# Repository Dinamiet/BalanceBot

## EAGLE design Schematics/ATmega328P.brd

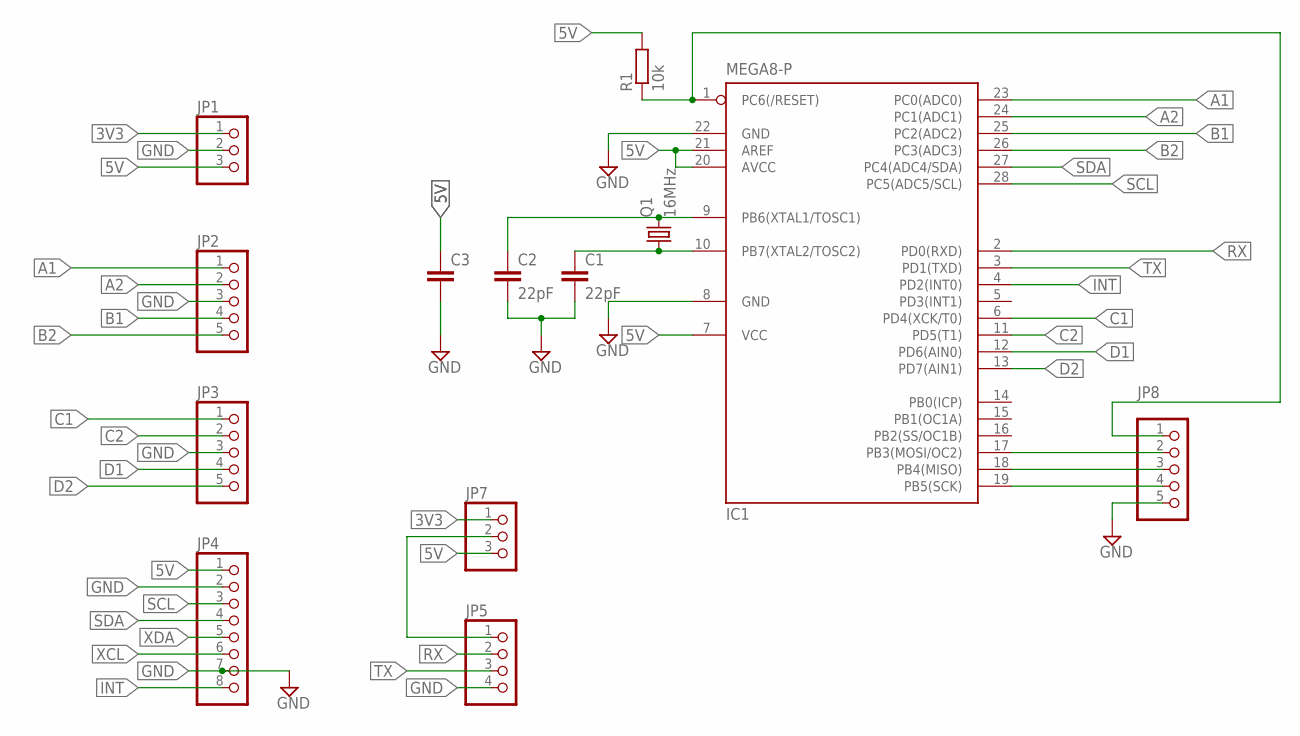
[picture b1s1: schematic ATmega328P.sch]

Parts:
C1, C2: 22pF; C2.5-2
C3: C2.5/2; C2.5-2
IC1: MEGA8-P; DIL28-3
JP1: PINHD-1X3/90; 1X03/90
JP2, JP3: PINHD-1X5/90; 1X05/90
JP4: PINHD-1X8/90; 1X08/90
JP5: PINHD-1X4/90; 1X04/90
JP7: PINHD-1X3; 1X03
JP8: PINHD-1X5; 1X05
Q1: 16MHz; HC49/S
R1: 10k; 0207/10

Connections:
3V3: JP1.1, JP7.1
5V: C3.1, IC1.7 (VCC), IC1.20 (AVCC), IC1.21 (AREF), JP1.3, JP4.1, JP7.3, R1.2
A1: IC1.23 (PC0(ADC0)), JP2.1
A2: IC1.24 (PC1(ADC1)), JP2.2
B1: IC1.25 (PC2(ADC2)), JP2.4
B2: IC1.26 (PC3(ADC3)), JP2.5
C1: IC1.6 (PD4(XCK/T0)), JP3.1
C2: IC1.11 (PD5(T1)), JP3.2
D1: IC1.12 (PD6(AIN0)), JP3.4
D2: IC1.13 (PD7(AIN1)), JP3.5
GND: C1.2, C2.2, C3.2, IC1.8 (GND), IC1.22 (GND), JP1.2, JP2.3, JP3.3, JP4.2, JP4.7, JP5.4, JP8.5
INT: IC1.4 (PD2(INT0)), JP4.8
unnamed: C2.1, IC1.9 (PB6(XTAL1/TOSC1)), Q1.2
unnamed: C1.1, IC1.10 (PB7(XTAL2/TOSC2)), Q1.1
unnamed: JP5.1, JP7.2
unnamed: IC1.19 (PB5(SCK)), JP8.4
unnamed: IC1.18 (PB4(MISO)), JP8.3
unnamed: IC1.17 (PB3(MOSI/OC2)), JP8.2
unnamed: IC1.1 (PC6(/RESET)), JP8.1, R1.1
RX: IC1.2 (PD0(RXD)), JP5.2
SCL: IC1.28 (PC5(ADC5/SCL)), JP4.3
SDA: IC1.27 (PC4(ADC4/SDA)), JP4.4
TX: IC1.3 (PD1(TXD)), JP5.3
XCL: JP4.6
XDA: JP4.5

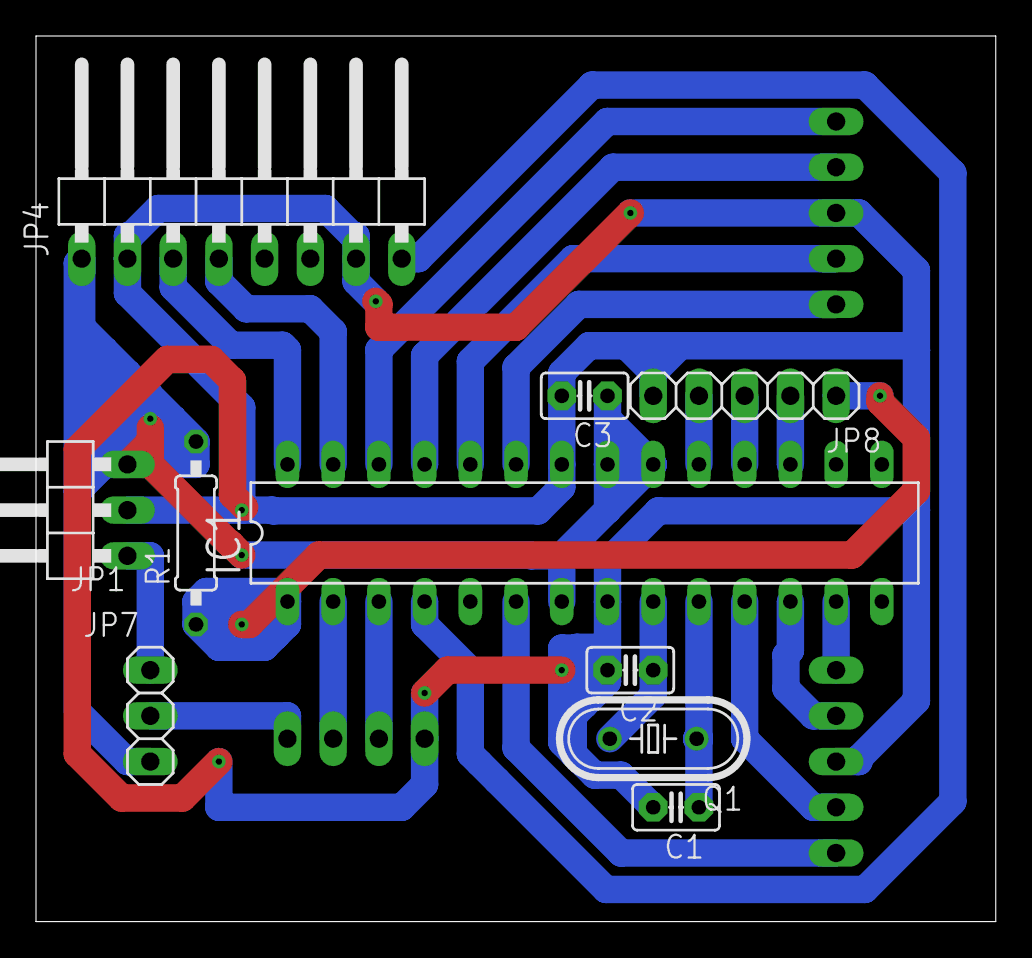
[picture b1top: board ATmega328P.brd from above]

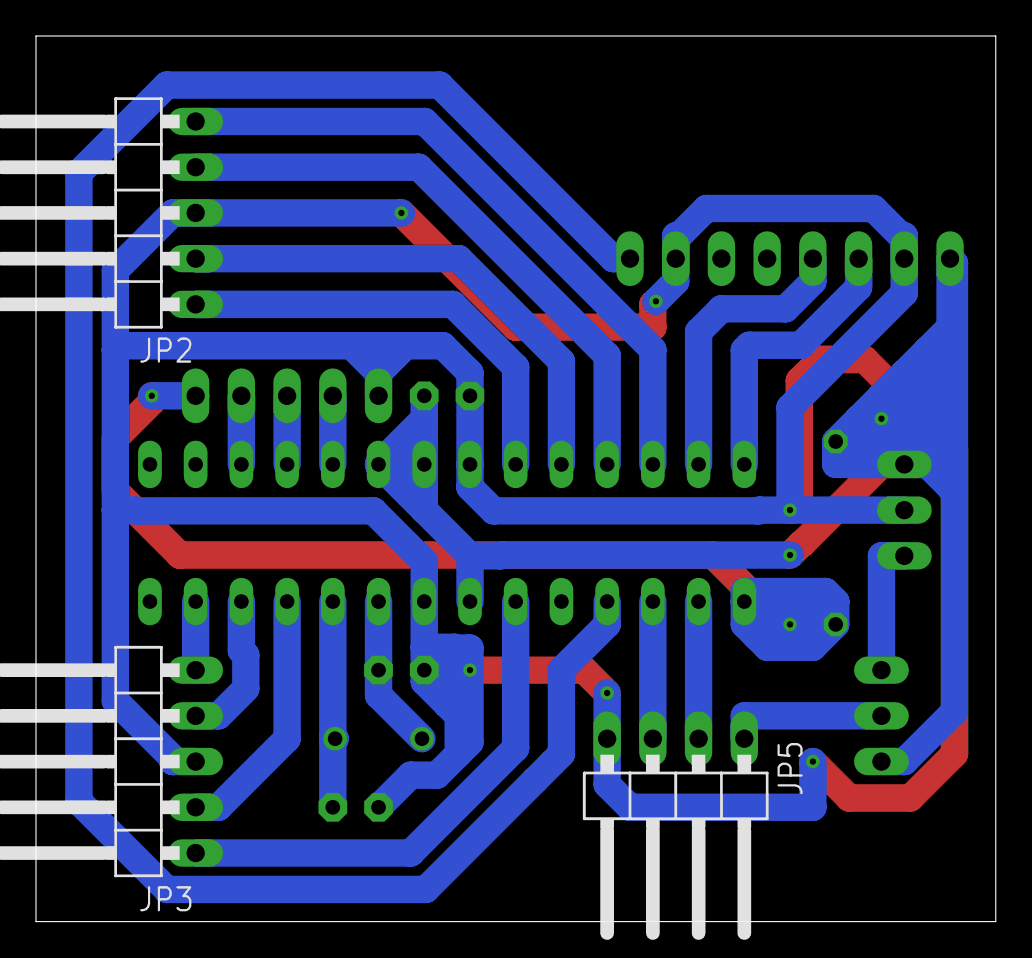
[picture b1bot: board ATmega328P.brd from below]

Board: 2 copper layers, 53.3 x 49.2 mm, 13 parts (3 on the bottom side), 23 nets.

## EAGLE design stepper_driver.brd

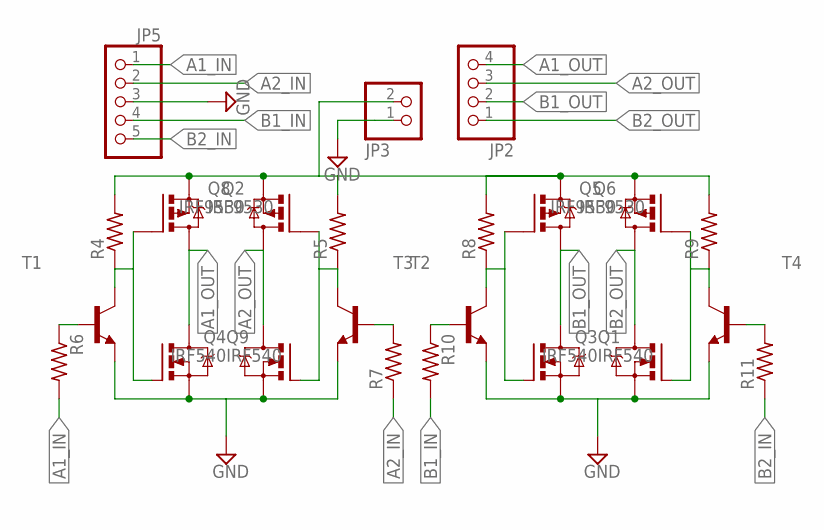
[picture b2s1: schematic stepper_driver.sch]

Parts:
JP2: PINHD-1X4/90; 1X04/90
JP3: PINHD-1X2/90; 1X02/90
JP5: PINHD-1X5/90; 1X05/90
Q1, Q3, Q4, Q9: IRF540; TO220BV
Q2, Q5, Q6, Q8: IRF9530; TO220BV
R4, R5, R6, R7, R8, R9, R10, R11: R-US_0309/10; 0309/10
T1, T2, T3, T4: 2N2222-NPN-TO92-EBC; TO92-EBC

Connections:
A1_IN: JP5.1, R6.2
A1_OUT: JP2.4, Q8.D, Q9.D
A2_IN: JP5.2, R7.1
A2_OUT: JP2.3, Q2.D, Q4.D
B1_IN: JP5.4, R10.2
B1_OUT: JP2.2, Q1.D, Q5.D
B2_IN: JP5.5, R11.1
B2_OUT: JP2.1, Q3.D, Q6.D
GND: JP3.1, JP5.3, Q1.S, Q3.S, Q4.S, Q9.S, T1.E, T2.E, T3.E, T4.E
unnamed: JP3.2, Q2.S, Q5.S, Q6.S, Q8.S, R4.2, R5.2, R8.2, R9.2
unnamed: Q2.G, Q4.G, R5.1, T2.C
unnamed: R7.2, T2.B
unnamed: Q1.G, Q5.G, R8.1, T3.C
unnamed: Q3.G, Q6.G, R9.1, T4.C
unnamed: Q8.G, Q9.G, R4.1, T1.C
unnamed: R6.1, T1.B
unnamed: R11.2, T4.B
unnamed: R10.1, T3.B

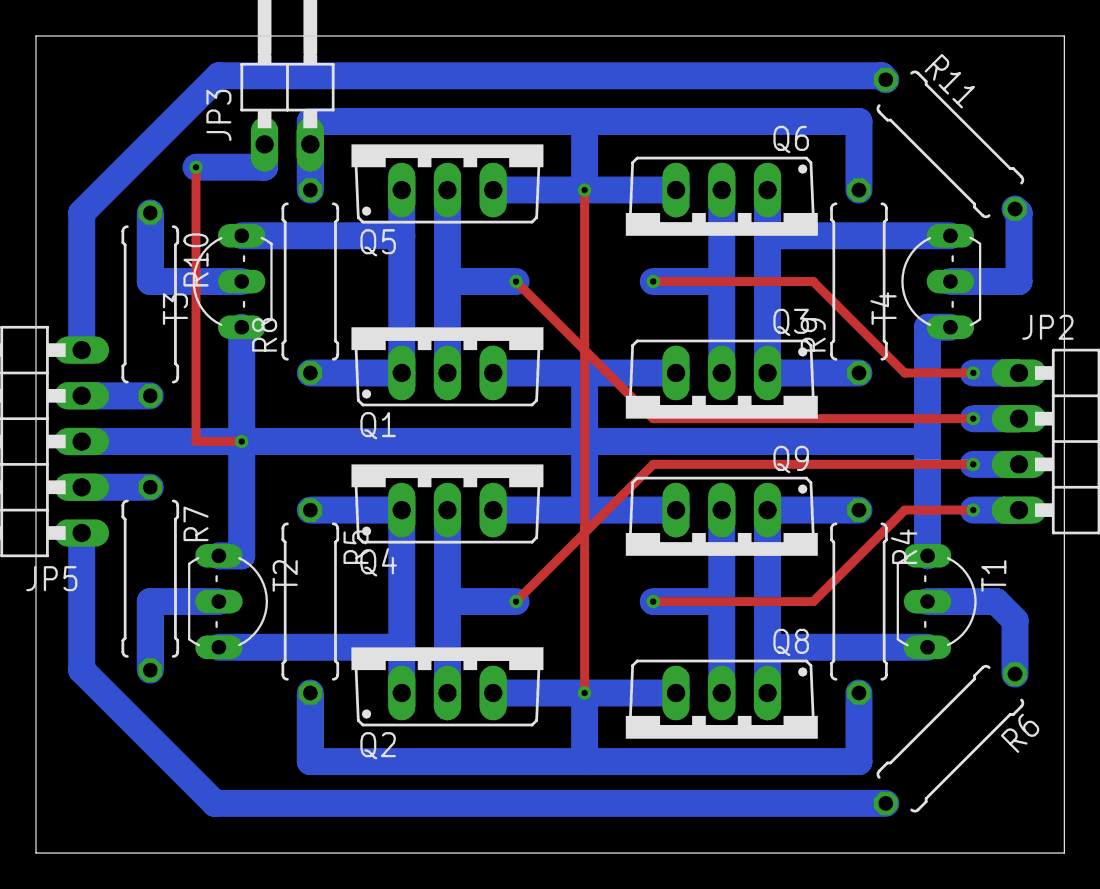
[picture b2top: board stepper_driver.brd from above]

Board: 2 copper layers, 57.1 x 45.4 mm, 23 parts (0 on the bottom side), 18 nets.

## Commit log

2019-11-02 Basic Read of data from IMU
2019-11-02 Using signed value for data
2019-11-02 Some tuning to code
2019-11-02 Split into functions
2019-11-02 Added formatting file for consistent code
2019-11-02 Moved functions to classes and seperate files
2019-11-02 Formatted code
2019-11-02 Updated formatter settings
2019-11-28 Added initialization
2019-11-28 Added INT enable and sample rate adjustments
2019-11-30 Streamlining library
2019-12-01 Added some DMP initialization code
2019-12-01 Up and working RAW values
2019-12-01 Writing DMP program to memory
2019-12-01 Using readBytes for RAW values
2019-12-01 Added FIFO count and int status
2019-12-02 Renamed DMP program memory
2019-12-02 Corrected Programming of DMP, added FIFO count func
2019-12-02 Added offsets
2019-12-02 Renamed DMP program memory files
2019-12-02 Little bit of cleanup and still needed functions added
2019-12-02 Renamed IMU to MPU6050
2019-12-02 Added some data structures to help with the math
2019-12-02 Getting yaw pitch and roll function added
2019-12-02 Getting RAW values from Registers. Using other Gyro and Accel data in FIFO packet
2019-12-02 Some renaming and restructuring
2019-12-02 Returning number of full packets available
2019-12-02 Ending I2C transmissions to release bus
2019-12-03 PID class implemented
2019-12-03 Added Gyro and Accel calibration routines
2019-12-03 Calibrating Gyro and Accel on startup
2019-12-07 Added motor driver simulation and circuit
2019-12-07 Added log and raw files
2019-12-08 Added Stepper motor library
2019-12-08 Basic initialization of Steppers
2019-12-15 Stepper motors will be steped every STEPSPEED interval
2019-12-15 UNO datasheet
2019-12-15 Controller board layout
2019-12-15 Controller board layout and schematic
2019-12-21 Moved components to their own repos
2019-12-21 Updated layout
2019-12-21 Ignoring CAM output from eagle
2019-12-21 Some adjustments to ISP, pin order matches arduino ISP
2019-12-24 Added Serial divider for 12MHz crystal
2020-01-11 Added correct stepper motor pins
2020-01-18 Bit of a bang bang approach but everything works
2020-01-18 Added PID control
2020-01-18 Little bit of tuning
2020-01-26 Fixed motor direction
2020-01-26 Tuned IMU calibration
2020-01-26 Added easier configurable switchoff angle
2020-01-26 PID fed constant dt
2020-01-26 Little bit of PID tuning
2020-01-26 Wait for IMU to be ready
2020-01-26 Moved PID into IMU new data check
2020-01-26 Some tunning
2020-10-04 Start balancing when starting to fall from pickup
2020-10-11 Added defines for cleaner code
2020-10-11 Updated Calibration and PID values
2021-09-26 Moved files around
2021-09-26 Minimal SW layout
2021-09-26 Moved Toolchains to SW directory
2021-09-26 Add Regulator and stepper driver schematics
2021-09-26 Add Serial library
2021-09-26 Create setup source to handle all setup operations
2021-09-26 Add CLI library
2021-09-26 Readme of needed and used libraries
2021-09-26 Code formatting update
2021-09-26 Add CLI setup and usage
2021-09-26 CLI library update
2021-09-28 Add system time timer
2021-09-28 Add task scheduler
2021-09-28 Use tasks
2021-09-28 Add GPIO
2021-09-28 LED toggle task
2021-10-02 Adapted for task scheduler multithreading update
2021-10-02 Disable interrupts when getting time to prevent time glitches
2021-10-02 Improved system time
2021-10-02 Task library improvements include
2021-10-02 Initial Stepper implementation
2021-10-02 Add Stepper step sequence
2021-10-03 Stepper output handling
2021-10-03 Stepper implementation
2021-10-09 Include new CLI help structure
2021-10-09 Improved taskscheduler timing
2021-10-09 Added more commands
2021-10-09 Include improve CLI
2021-10-09 Add additional modules
2021-10-09 Started with IMU integration
2021-10-09 Library updates
2021-10-14 IMU fixes import
2021-10-15 Code structure refactoring effort
2021-10-15 IMU commands added
2021-10-15 IMU implemented
2021-10-15 Cmd help strings removed to save space
2021-10-15 Add Control loop
2021-10-15 Control angle subscription
2021-10-16 Space saving by reducing string lenghts
2021-10-16 Little tuning
2021-11-21 PID tuning
2021-11-21 Removed full step setup. Can skip halfstep and do full step if required.
2021-12-26 Toolchain update
2024-10-05 Clean workspace
2024-10-05 Add toolchain
2024-10-05 Basic hello world startup
2024-10-05 UART initialization to own file
2024-10-05 Rename uart setup
2024-10-05 Add CLI
2024-10-05 Add system timer
2024-10-05 Remove submodules
2024-10-06 Add I2C driver
2024-10-06 I2C bus scan command added
2024-10-07 Add IMU
2024-10-07 Faster I2C and bigger buffer
2024-10-09 Add imu command for calibration
2024-10-10 Program offsets as part of setup
2024-10-10 Checking IMU interrupt and reading data
2024-10-12 Welcome message and delay IMU configure a bit longer
2024-10-12 Dont request data in callbacks
2024-10-13 Rename ATMega to AVR
2024-10-18 Nonblocking CLI write
2024-10-18 Increase I2C and UART buffers as space is available
2024-10-18 Update I2C functions to conform to updated I2C library
2024-10-18 Non blocking CLI as far as possible
2024-10-18 Faster I2C (400kHz)
2024-10-18 IMU callback updates
2024-10-18 Faster BAUD rate with low enough error rate
2024-10-18 Code and output formatting
2024-10-20 Print Yaw Pitch Roll out to console
2024-10-20 Enable float print formatting
2024-10-22 Observer for IMU data
2024-10-22 Tasks naming updated
2024-10-24 Add Motor control from old implementation - this still needs some improvement
2024-10-24 Control loop closed :)
2024-10-24 Runtime configurable PID
2024-10-24 Adjustable target angle
2024-10-24 No motor jerking on startup
2024-11-18 Add stepper and data communication library
2024-11-18 Remove CLI
2024-11-19 Remove floating print support
2024-11-19 Implement stepper library for motor control
2024-11-20 Added configuration interface
2024-11-20 Add NULL termination to messages list
2024-11-23 Config app layout
2024-11-23 Reading data from serial port
2024-11-23 Receiving heartbeat message
2024-11-26 Add imu command for calibration and subscribing
2024-11-27 Add IMU data handler message
2024-11-28 Added more commands to Config App
2024-11-28 Add message handlers
2024-11-28 Implement request handlers for messages
2024-11-28 Fix datascaling
2024-11-29 Add exit command to close application
2024-11-29 Fix printouts of Config App
2024-11-29 Handle unsub from imu data
2024-11-29 Add windup prevention
2024-11-29 Stepper driver change
2024-11-29 Add motor command
2024-11-29 Faster motor stepping
2024-11-30 Update motor pins for newly installed drivers
2024-11-30 Add step size configuration motor message
2024-11-30 Only send every 25 IMU data samples if subscribed to it to prevent bus overflow
2024-12-01 Fix print color problems
2024-12-01 Fix offset prints
2024-12-01 Increase motor cooldown wait time and increase heartbeat frequency
2024-12-07 PID control structure alignement
2024-12-07 Add TCP connection
2024-12-07 Application arguments to select between Serial and TCP
2024-12-07 Cleaner source layout of serial interface
2024-12-07 Enable/disable heartbeat command
2024-12-07 Serial read timeout without need for data
2024-12-07 TCP receive timeout to continuously process data
2024-12-07 Recalibration
2024-12-07 Zero out PID values - need to retune
2024-12-08 Update PID control parameters
2024-12-08 Added step size description
2024-12-15 Motor speed option
2024-12-15 Position command
2024-12-16 Debug & position control updates
2024-12-16 Fairy okay balancing
2024-12-16 Debug enable/disable
2025-01-18 Migrate dependencies to github
2025-03-14 Add GitHub Sponsor configuration
